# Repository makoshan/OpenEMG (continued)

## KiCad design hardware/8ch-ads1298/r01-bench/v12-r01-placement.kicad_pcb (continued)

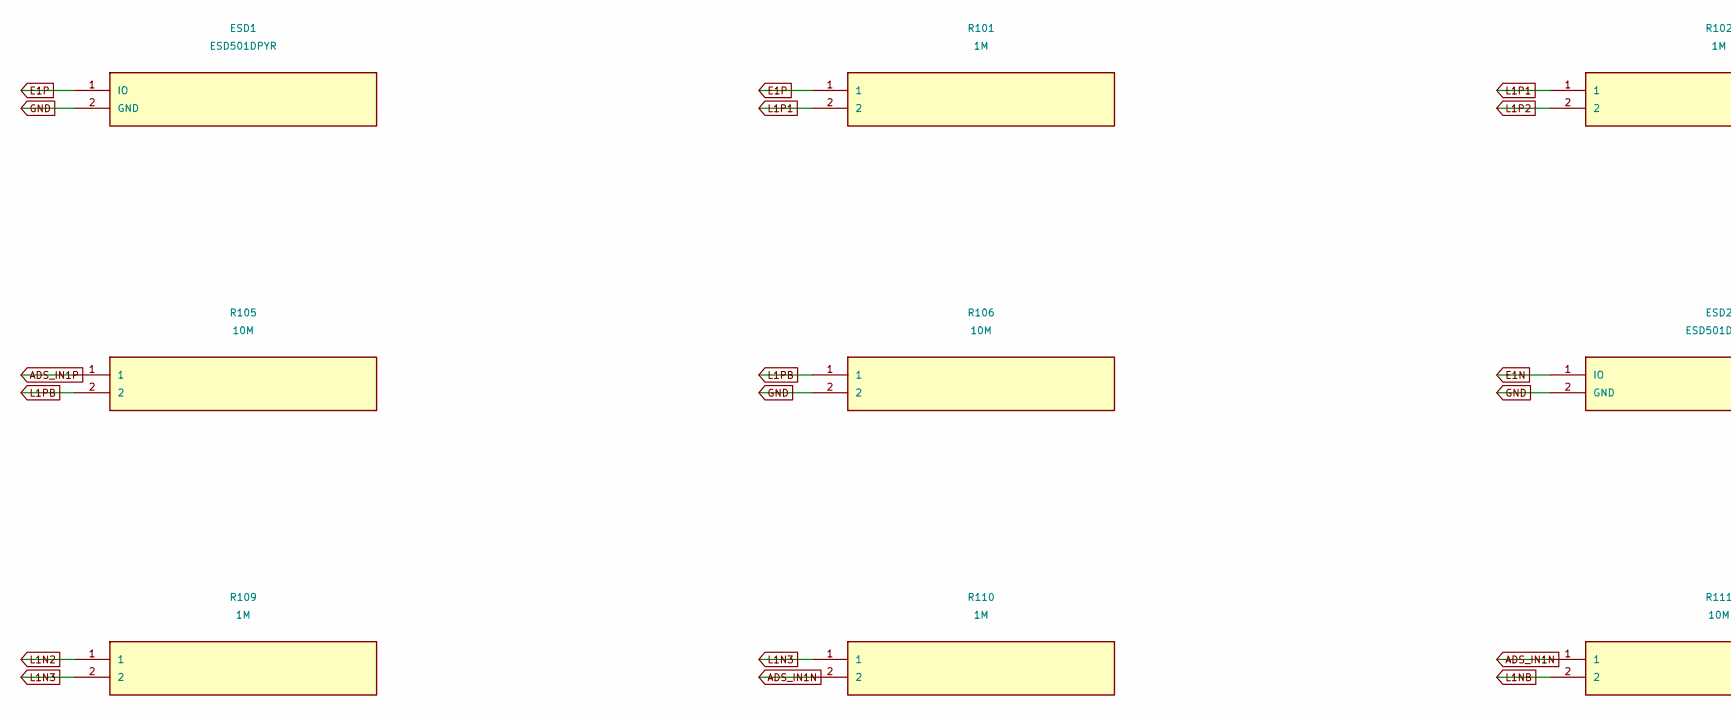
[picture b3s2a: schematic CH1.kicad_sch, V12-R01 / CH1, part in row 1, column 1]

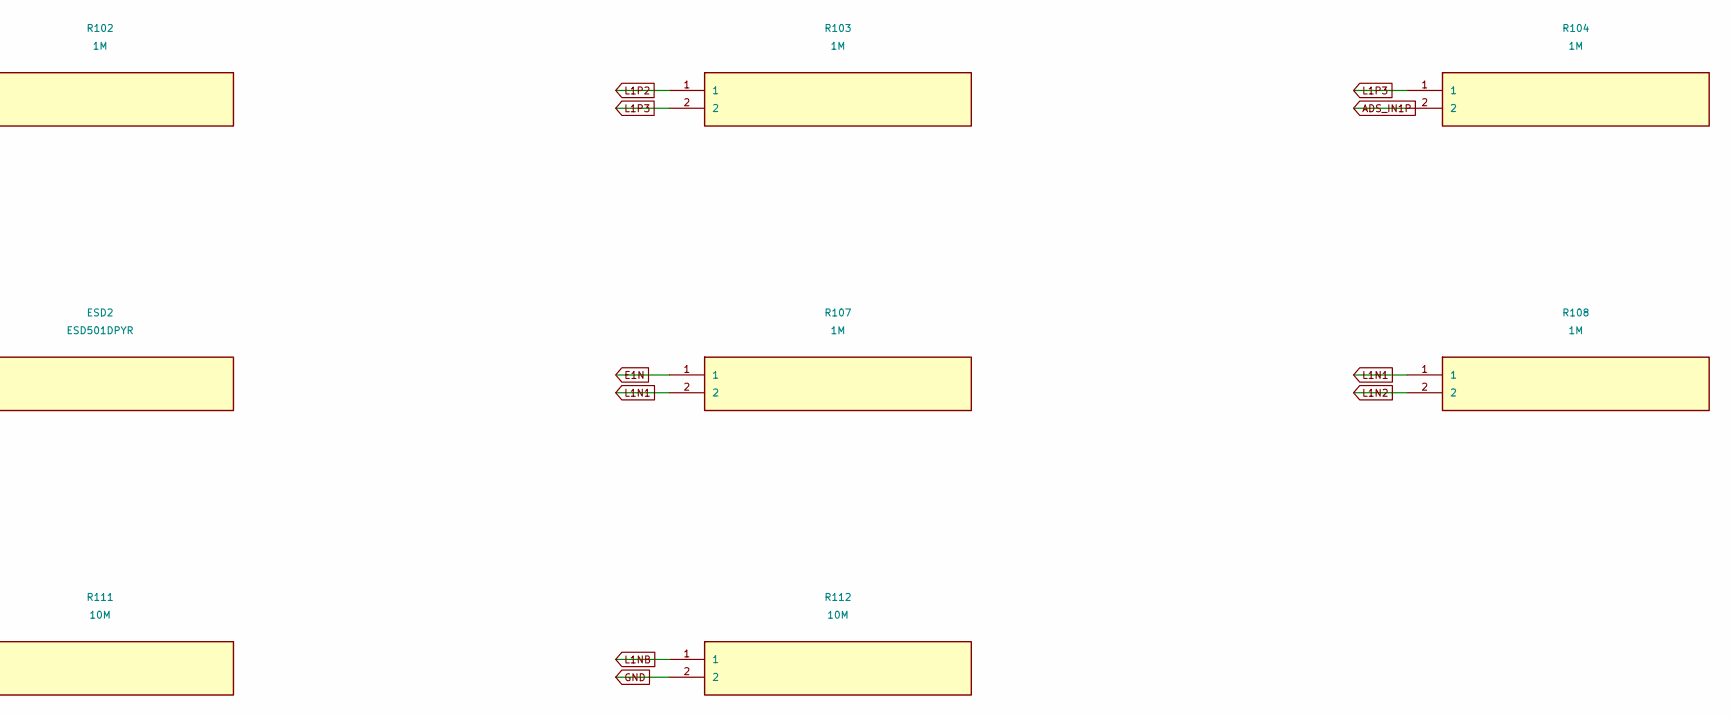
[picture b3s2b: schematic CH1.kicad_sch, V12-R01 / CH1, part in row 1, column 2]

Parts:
ESD1, ESD2: ESD501DPYR; Texas_DPY0002A_0.6x1mm_P0.65mm
R101, R102, R103, R104, R107, R108, R109, R110: 1M; R_0402_1005Metric
R105, R106, R111, R112: 10M; R_0402_1005Metric

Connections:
ADS_IN1N: R110.2, R111.1; also elsewhere on the board
ADS_IN1P: R104.2, R105.1; also elsewhere on the board
E1N: ESD2.1 (IO), R107.1; also elsewhere on the board
E1P: ESD1.1 (IO), R101.1; also elsewhere on the board
GND: ESD1.2 (GND), ESD2.2 (GND), R106.2, R112.2; also elsewhere on the board
L1N1: R107.2, R108.1
L1N2: R108.2, R109.1
L1N3: R109.2, R110.1
L1NB: R111.2, R112.1
L1P1: R101.2, R102.1
L1P2: R102.2, R103.1
L1P3: R103.2, R104.1
L1PB: R105.2, R106.1

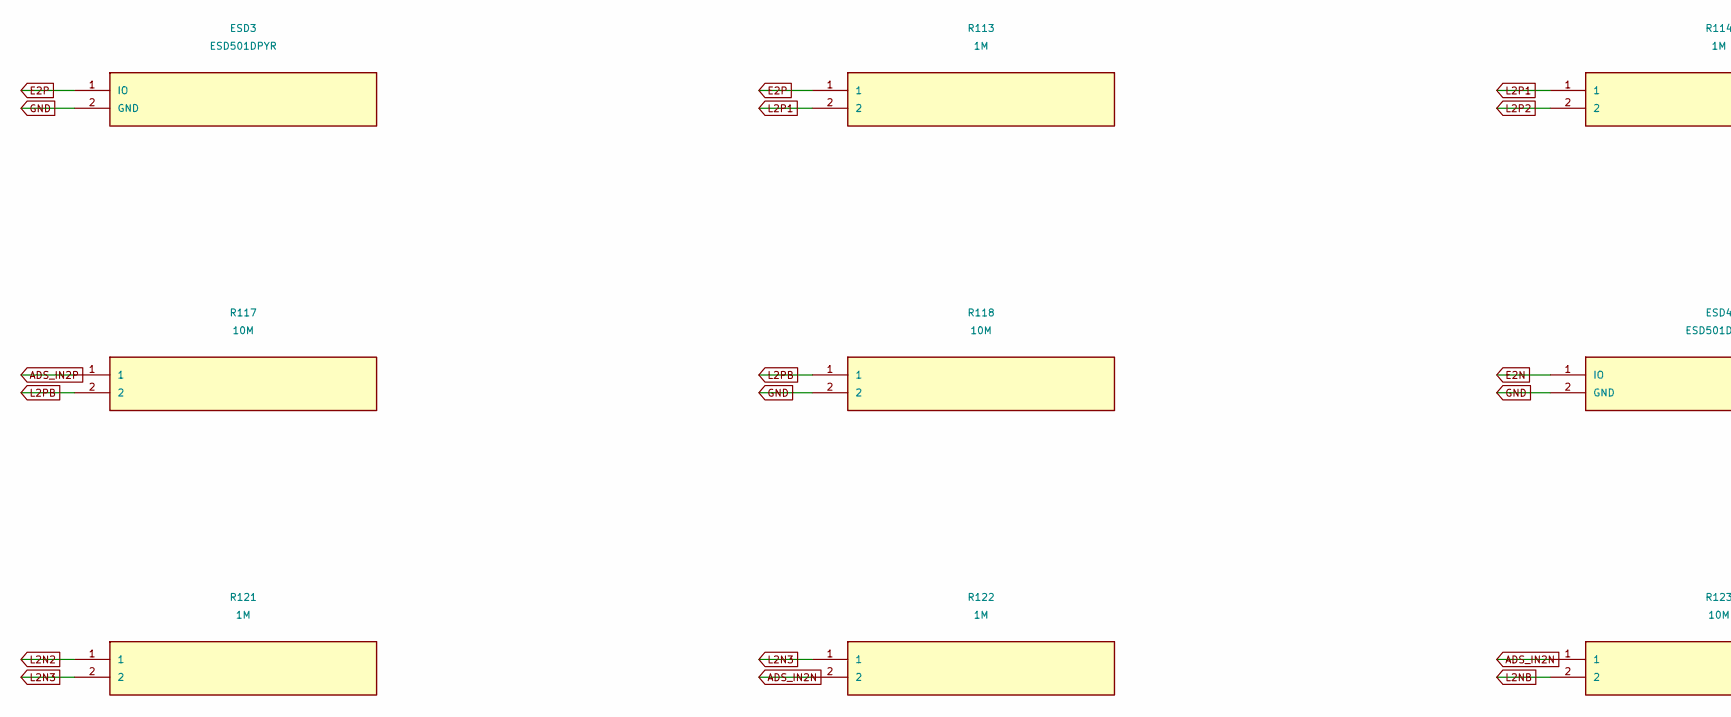
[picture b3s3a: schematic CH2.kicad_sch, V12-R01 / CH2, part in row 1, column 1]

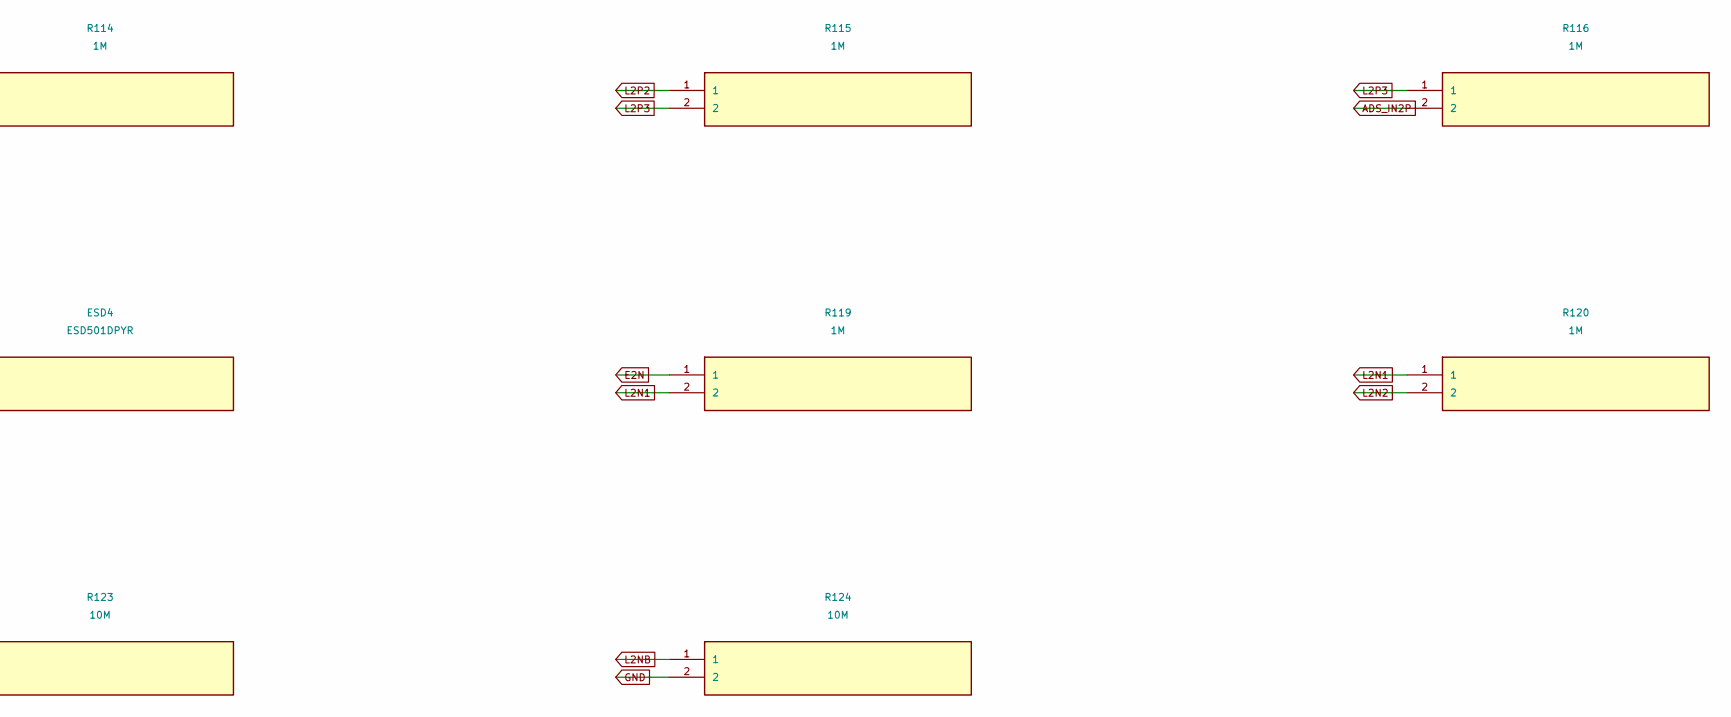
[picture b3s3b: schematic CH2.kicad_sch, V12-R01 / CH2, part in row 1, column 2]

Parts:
ESD3, ESD4: ESD501DPYR; Texas_DPY0002A_0.6x1mm_P0.65mm
R113, R114, R115, R116, R119, R120, R121, R122: 1M; R_0402_1005Metric
R117, R118, R123, R124: 10M; R_0402_1005Metric

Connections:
ADS_IN2N: R122.2, R123.1; also elsewhere on the board
ADS_IN2P: R116.2, R117.1; also elsewhere on the board
E2N: ESD4.1 (IO), R119.1; also elsewhere on the board
E2P: ESD3.1 (IO), R113.1; also elsewhere on the board
GND: ESD3.2 (GND), ESD4.2 (GND), R118.2, R124.2; also elsewhere on the board
L2N1: R119.2, R120.1
L2N2: R120.2, R121.1
L2N3: R121.2, R122.1
L2NB: R123.2, R124.1
L2P1: R113.2, R114.1
L2P2: R114.2, R115.1
L2P3: R115.2, R116.1
L2PB: R117.2, R118.1

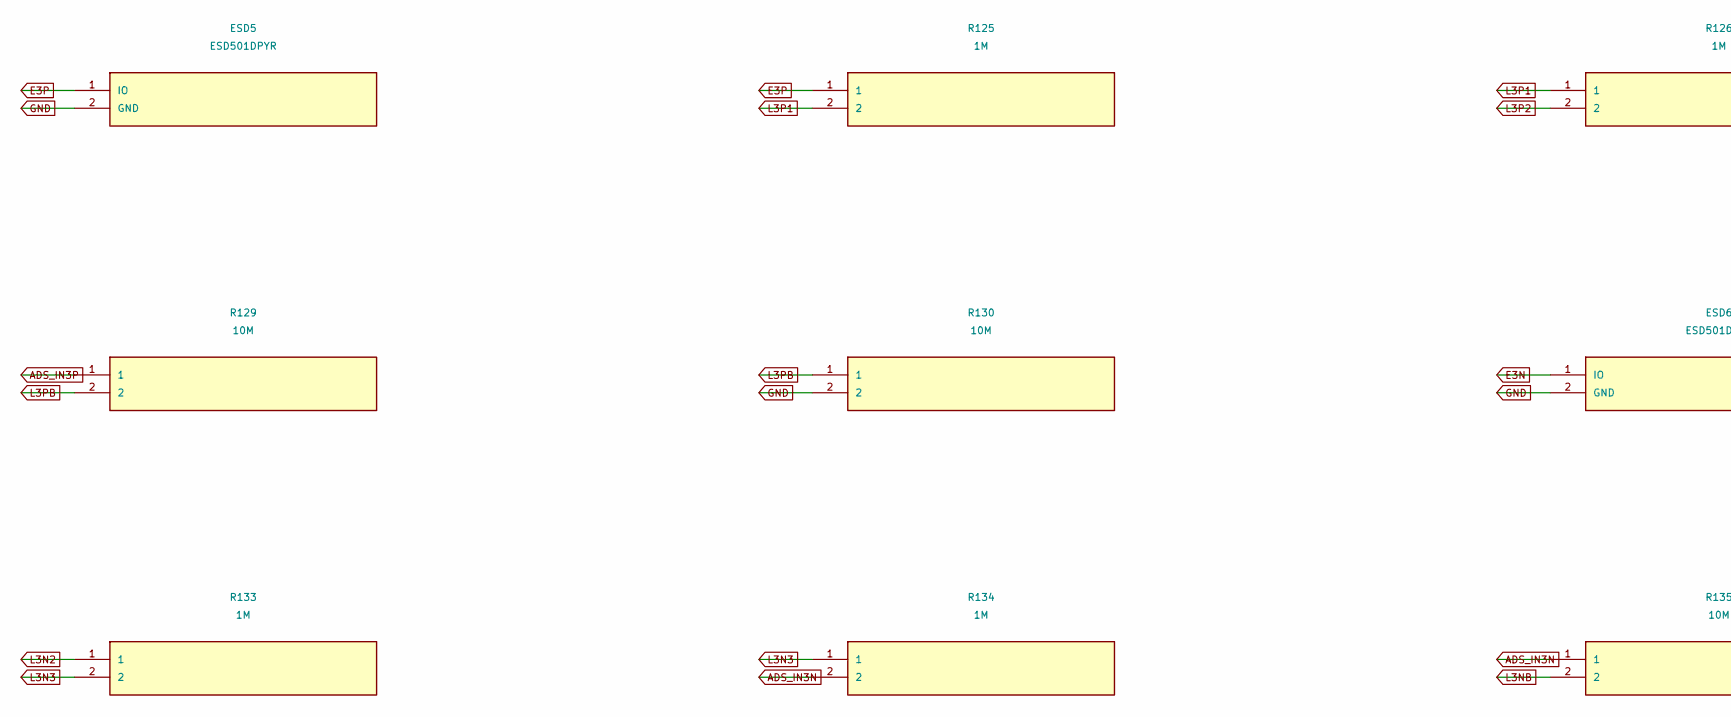
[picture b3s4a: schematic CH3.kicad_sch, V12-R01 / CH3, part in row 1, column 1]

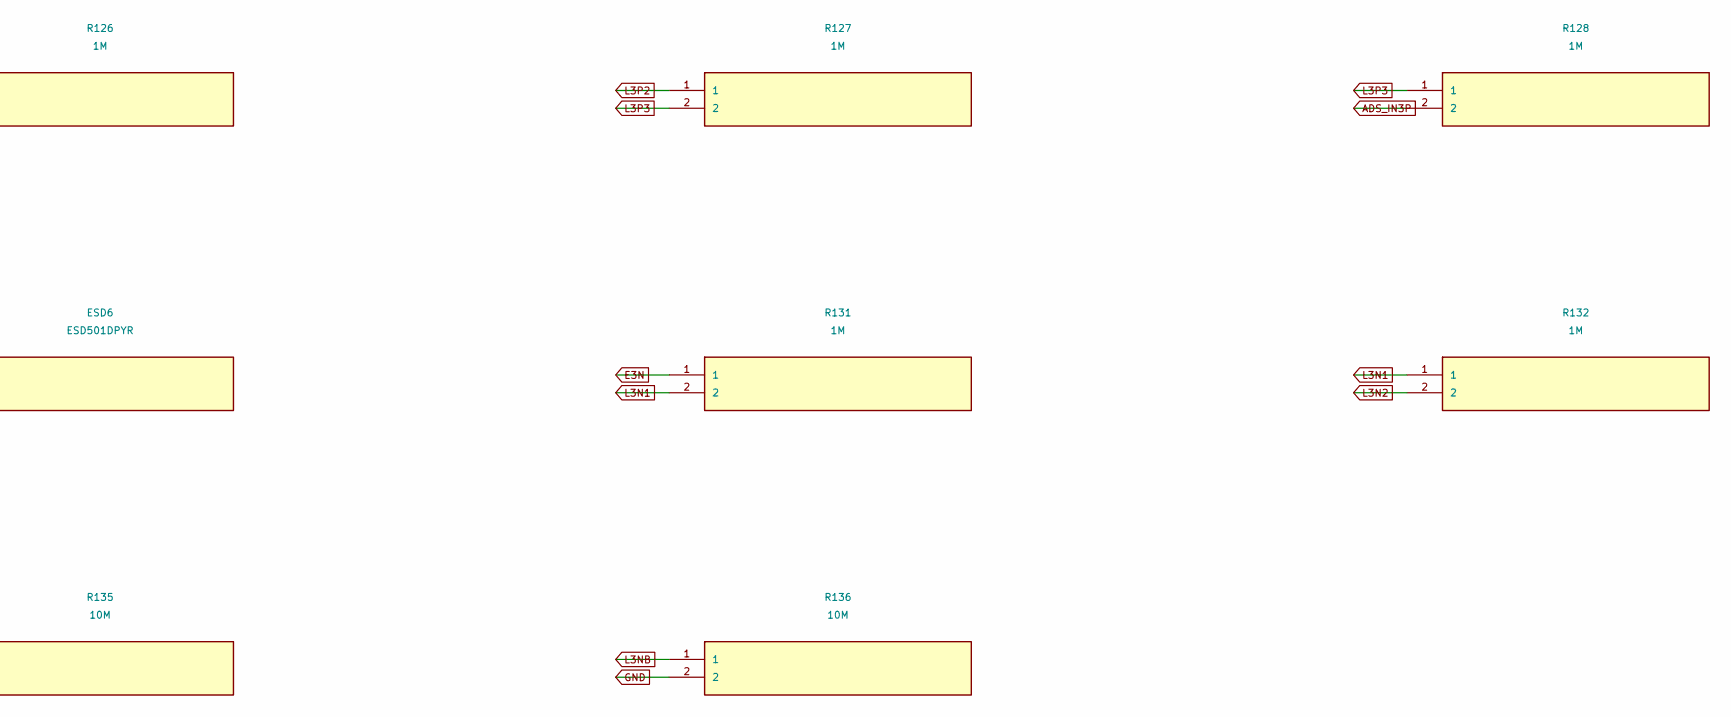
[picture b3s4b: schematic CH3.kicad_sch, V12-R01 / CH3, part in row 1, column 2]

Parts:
ESD5, ESD6: ESD501DPYR; Texas_DPY0002A_0.6x1mm_P0.65mm
R125, R126, R127, R128, R131, R132, R133, R134: 1M; R_0402_1005Metric
R129, R130, R135, R136: 10M; R_0402_1005Metric

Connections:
ADS_IN3N: R134.2, R135.1; also elsewhere on the board
ADS_IN3P: R128.2, R129.1; also elsewhere on the board
E3N: ESD6.1 (IO), R131.1; also elsewhere on the board
E3P: ESD5.1 (IO), R125.1; also elsewhere on the board
GND: ESD5.2 (GND), ESD6.2 (GND), R130.2, R136.2; also elsewhere on the board
L3N1: R131.2, R132.1
L3N2: R132.2, R133.1
L3N3: R133.2, R134.1
L3NB: R135.2, R136.1
L3P1: R125.2, R126.1
L3P2: R126.2, R127.1
L3P3: R127.2, R128.1
L3PB: R129.2, R130.1

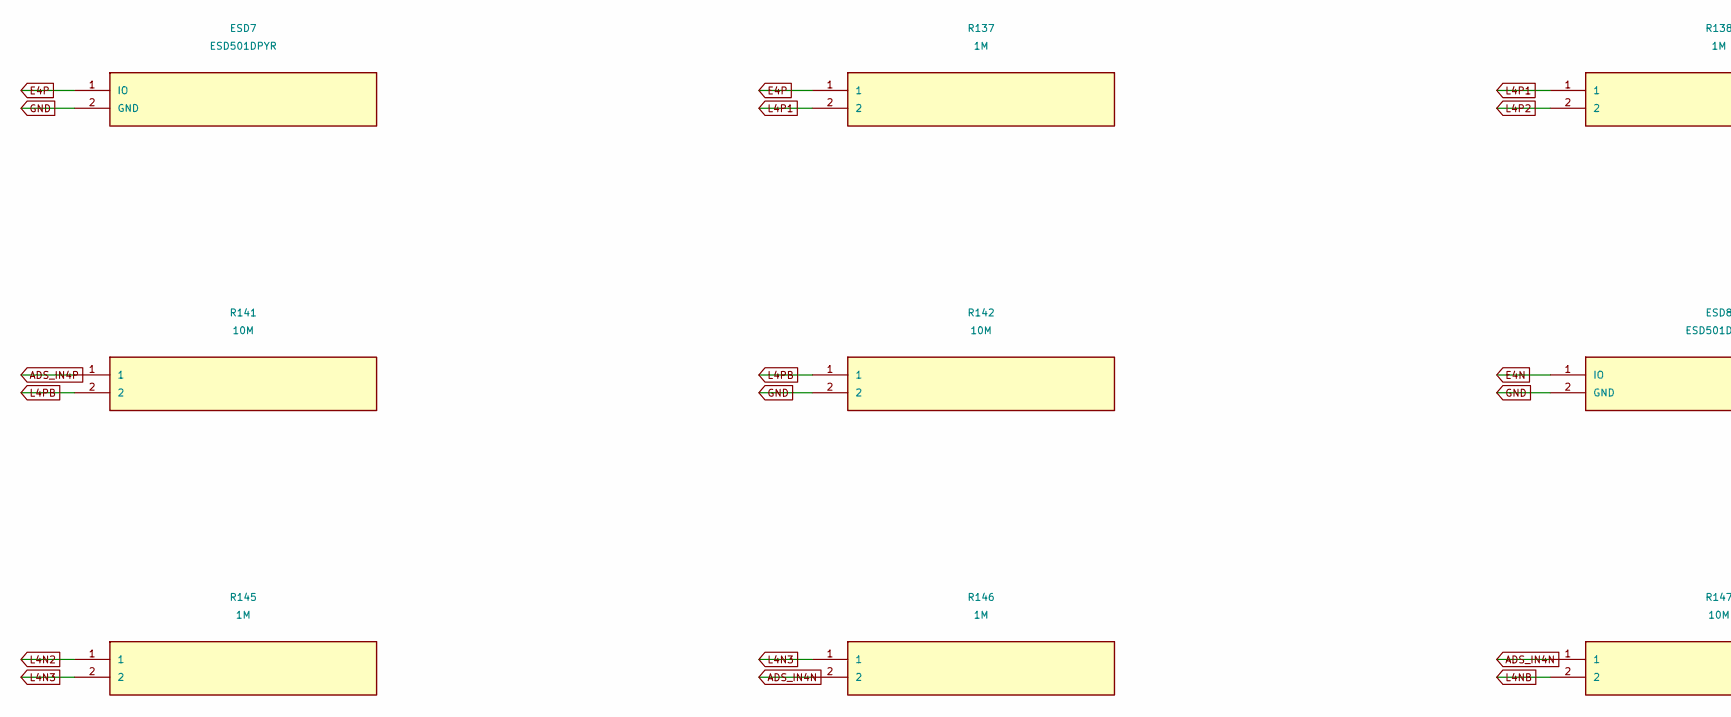
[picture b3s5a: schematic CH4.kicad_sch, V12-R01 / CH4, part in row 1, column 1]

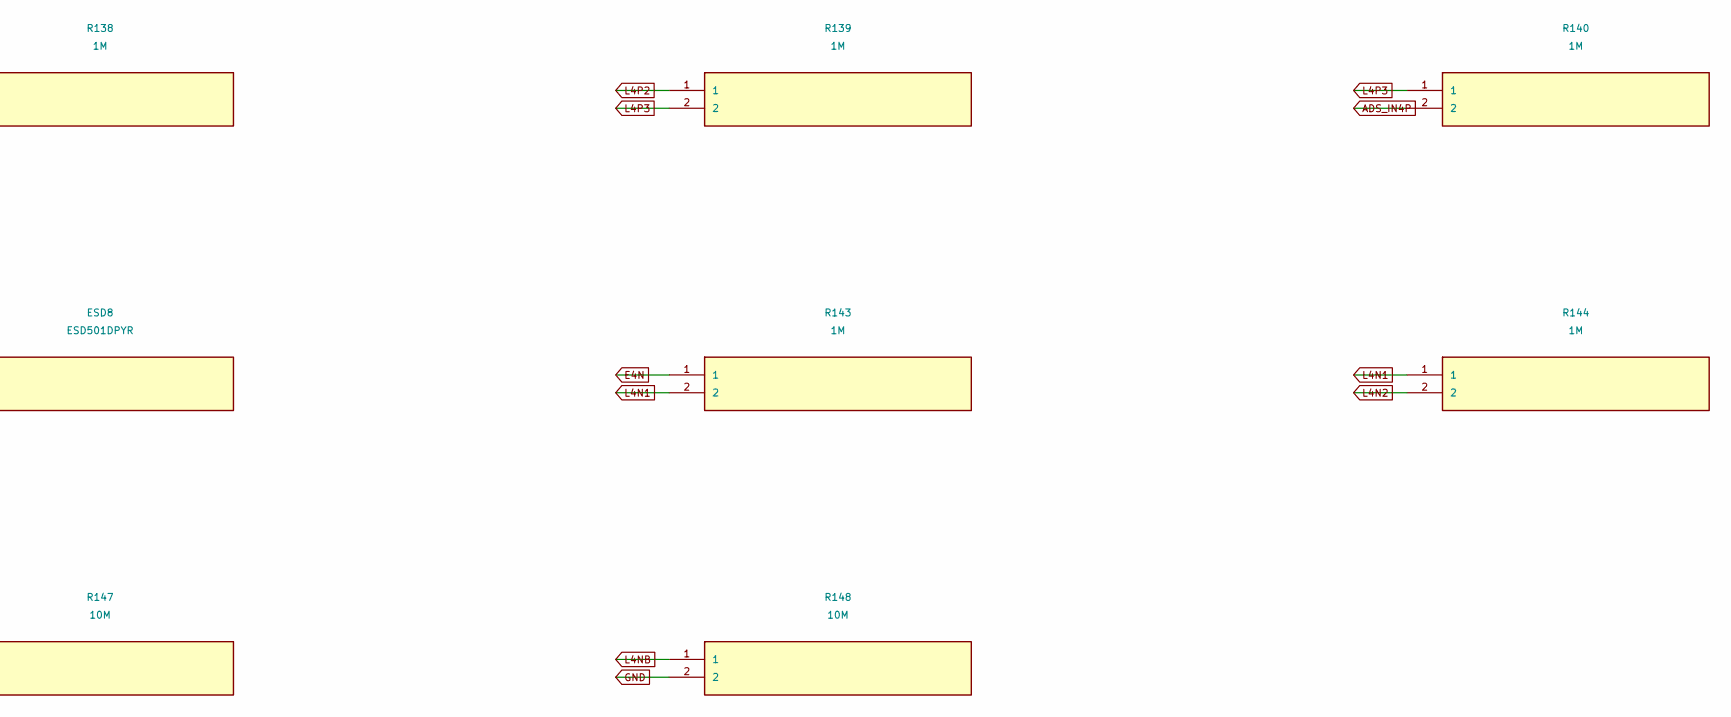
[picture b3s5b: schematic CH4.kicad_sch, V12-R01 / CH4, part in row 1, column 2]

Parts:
ESD7, ESD8: ESD501DPYR; Texas_DPY0002A_0.6x1mm_P0.65mm
R137, R138, R139, R140, R143, R144, R145, R146: 1M; R_0402_1005Metric
R141, R142, R147, R148: 10M; R_0402_1005Metric

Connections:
ADS_IN4N: R146.2, R147.1; also elsewhere on the board
ADS_IN4P: R140.2, R141.1; also elsewhere on the board
E4N: ESD8.1 (IO), R143.1; also elsewhere on the board
E4P: ESD7.1 (IO), R137.1; also elsewhere on the board
GND: ESD7.2 (GND), ESD8.2 (GND), R142.2, R148.2; also elsewhere on the board
L4N1: R143.2, R144.1
L4N2: R144.2, R145.1
L4N3: R145.2, R146.1
L4NB: R147.2, R148.1
L4P1: R137.2, R138.1
L4P2: R138.2, R139.1
L4P3: R139.2, R140.1
L4PB: R141.2, R142.1

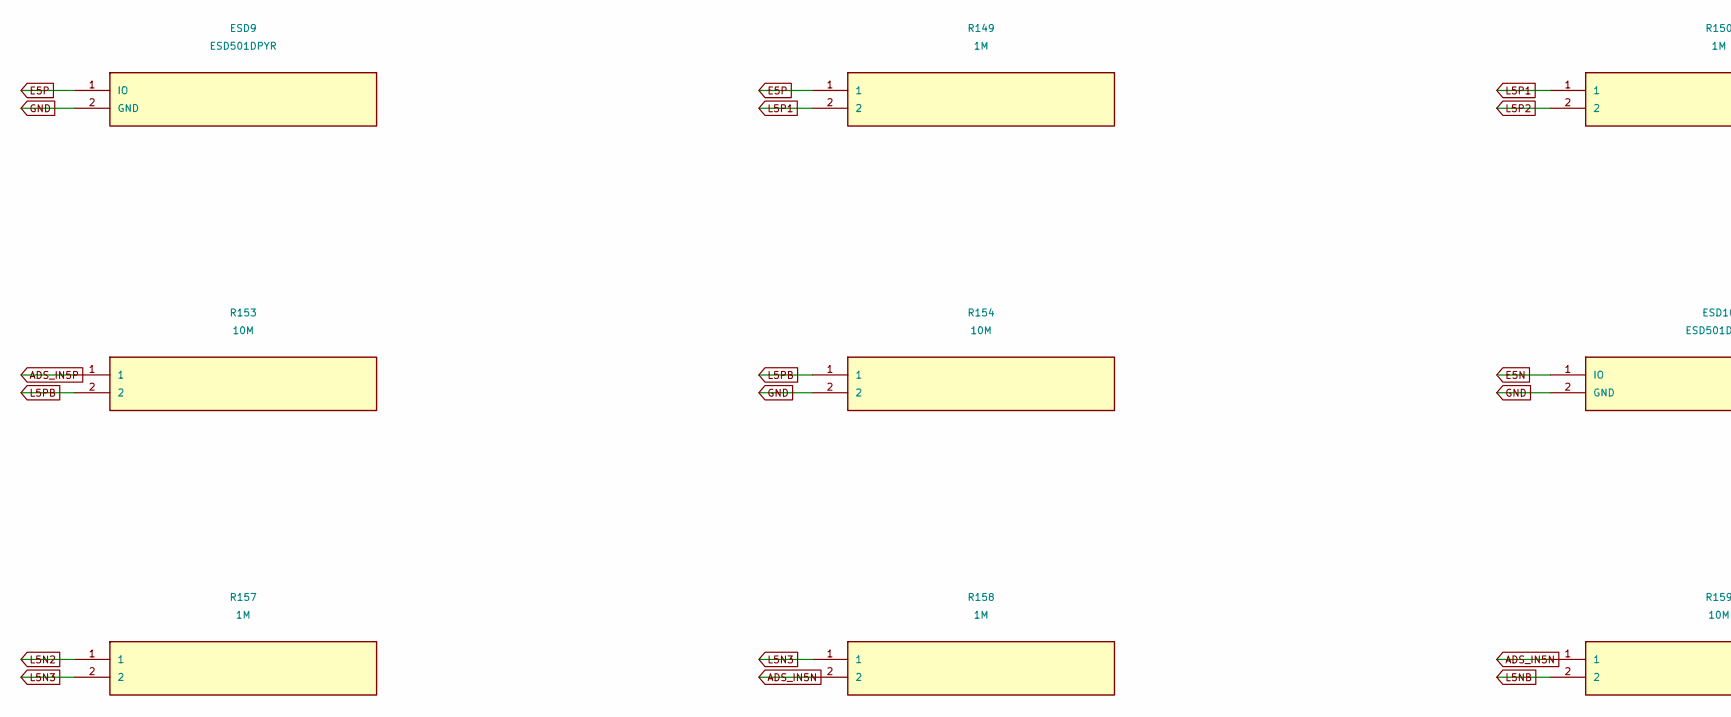
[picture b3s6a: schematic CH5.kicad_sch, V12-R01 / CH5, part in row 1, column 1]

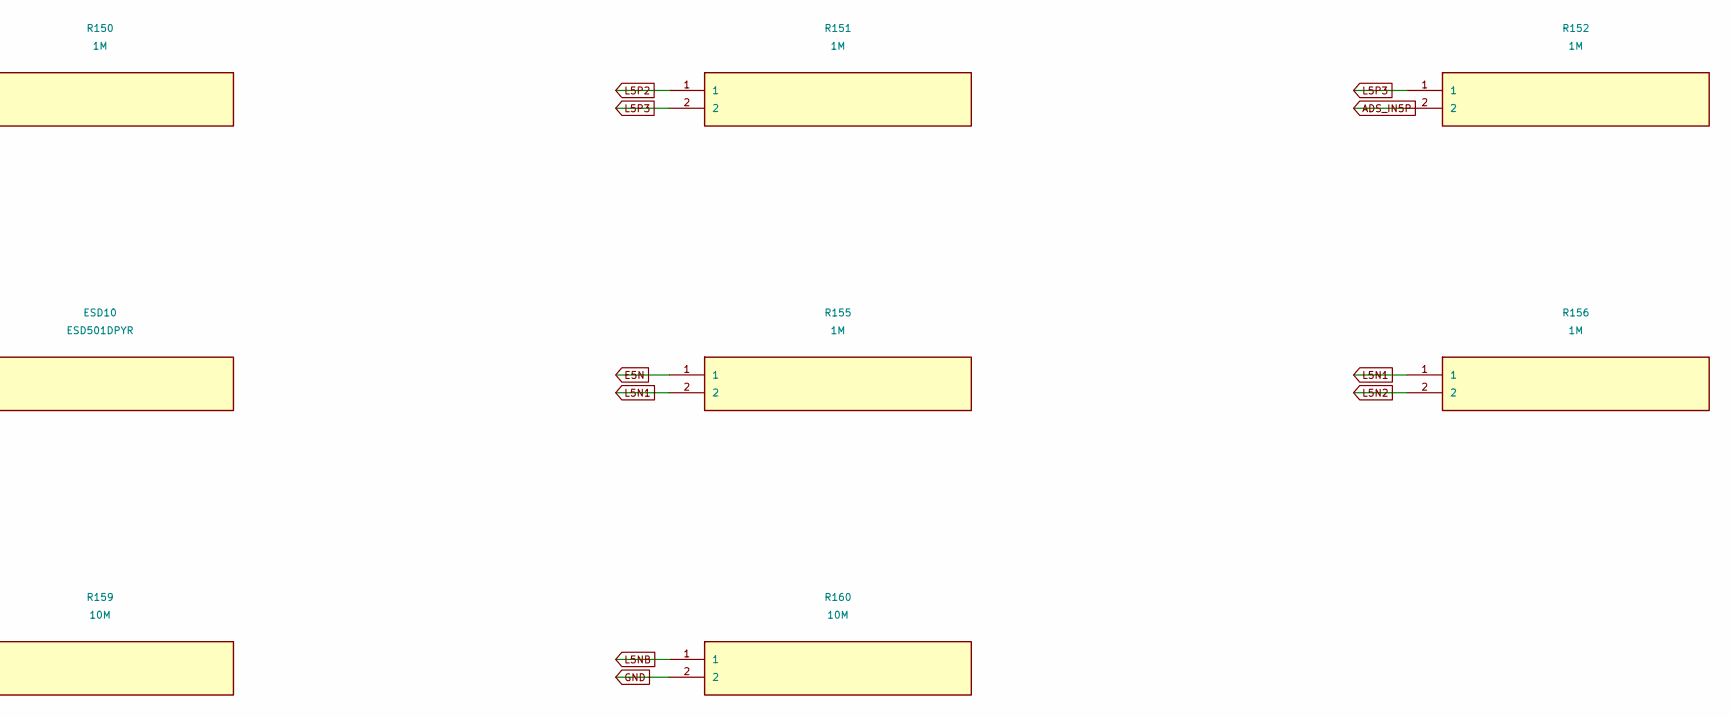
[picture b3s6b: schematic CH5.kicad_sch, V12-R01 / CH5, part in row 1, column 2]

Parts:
ESD9, ESD10: ESD501DPYR; Texas_DPY0002A_0.6x1mm_P0.65mm
R149, R150, R151, R152, R155, R156, R157, R158: 1M; R_0402_1005Metric
R153, R154, R159, R160: 10M; R_0402_1005Metric

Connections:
ADS_IN5N: R158.2, R159.1; also elsewhere on the board
ADS_IN5P: R152.2, R153.1; also elsewhere on the board
E5N: ESD10.1 (IO), R155.1; also elsewhere on the board
E5P: ESD9.1 (IO), R149.1; also elsewhere on the board
GND: ESD9.2 (GND), ESD10.2 (GND), R154.2, R160.2; also elsewhere on the board
L5N1: R155.2, R156.1
L5N2: R156.2, R157.1
L5N3: R157.2, R158.1
L5NB: R159.2, R160.1
L5P1: R149.2, R150.1
L5P2: R150.2, R151.1
L5P3: R151.2, R152.1
L5PB: R153.2, R154.1

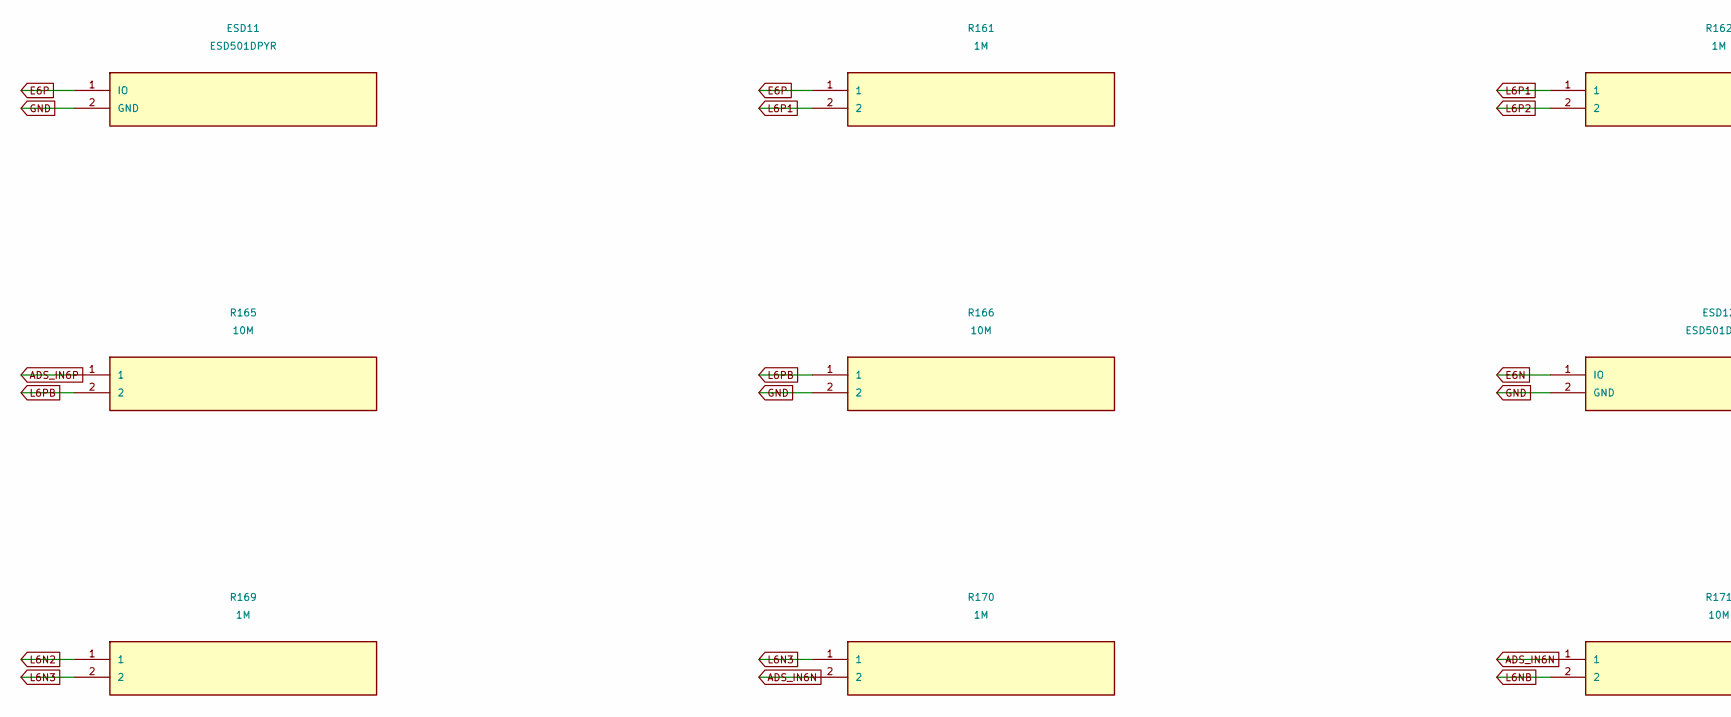
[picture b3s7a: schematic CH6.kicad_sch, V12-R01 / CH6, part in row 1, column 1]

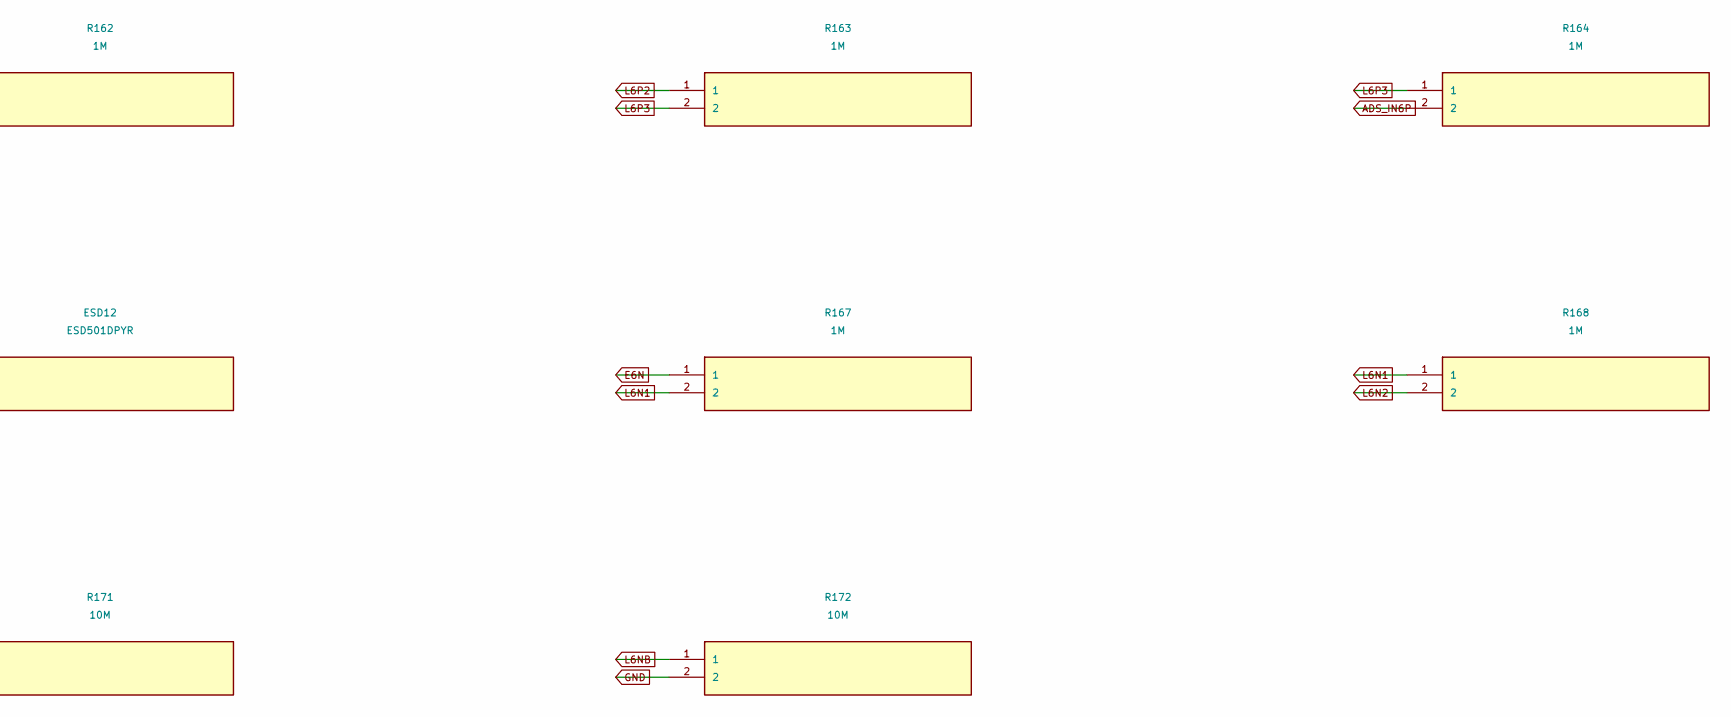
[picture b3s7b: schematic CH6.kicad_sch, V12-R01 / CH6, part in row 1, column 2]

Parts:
ESD11, ESD12: ESD501DPYR; Texas_DPY0002A_0.6x1mm_P0.65mm
R161, R162, R163, R164, R167, R168, R169, R170: 1M; R_0402_1005Metric
R165, R166, R171, R172: 10M; R_0402_1005Metric

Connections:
ADS_IN6N: R170.2, R171.1; also elsewhere on the board
ADS_IN6P: R164.2, R165.1; also elsewhere on the board
E6N: ESD12.1 (IO), R167.1; also elsewhere on the board
E6P: ESD11.1 (IO), R161.1; also elsewhere on the board
GND: ESD11.2 (GND), ESD12.2 (GND), R166.2, R172.2; also elsewhere on the board
L6N1: R167.2, R168.1
L6N2: R168.2, R169.1
L6N3: R169.2, R170.1
L6NB: R171.2, R172.1
L6P1: R161.2, R162.1
L6P2: R162.2, R163.1
L6P3: R163.2, R164.1
L6PB: R165.2, R166.1

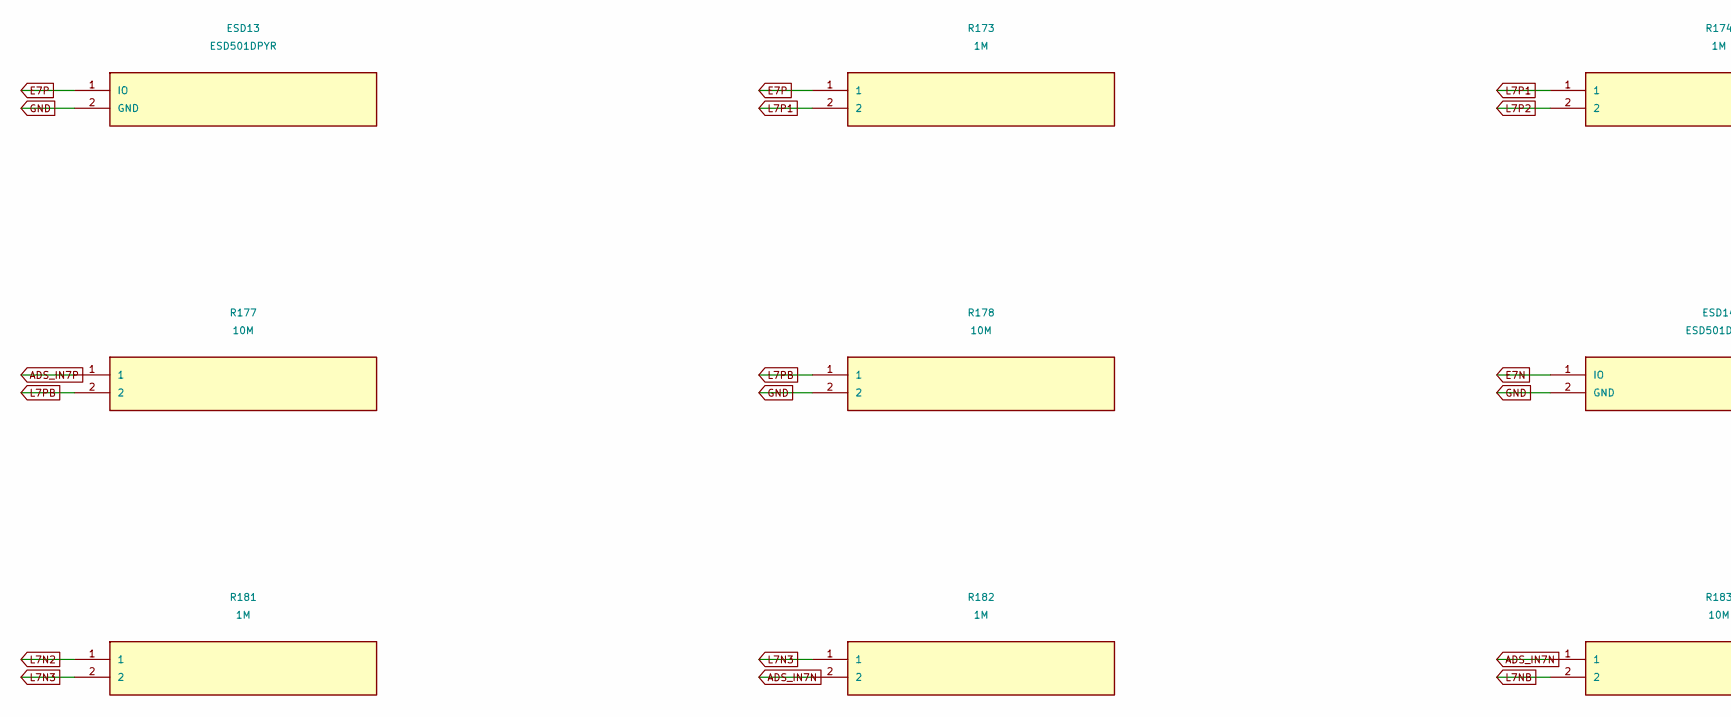
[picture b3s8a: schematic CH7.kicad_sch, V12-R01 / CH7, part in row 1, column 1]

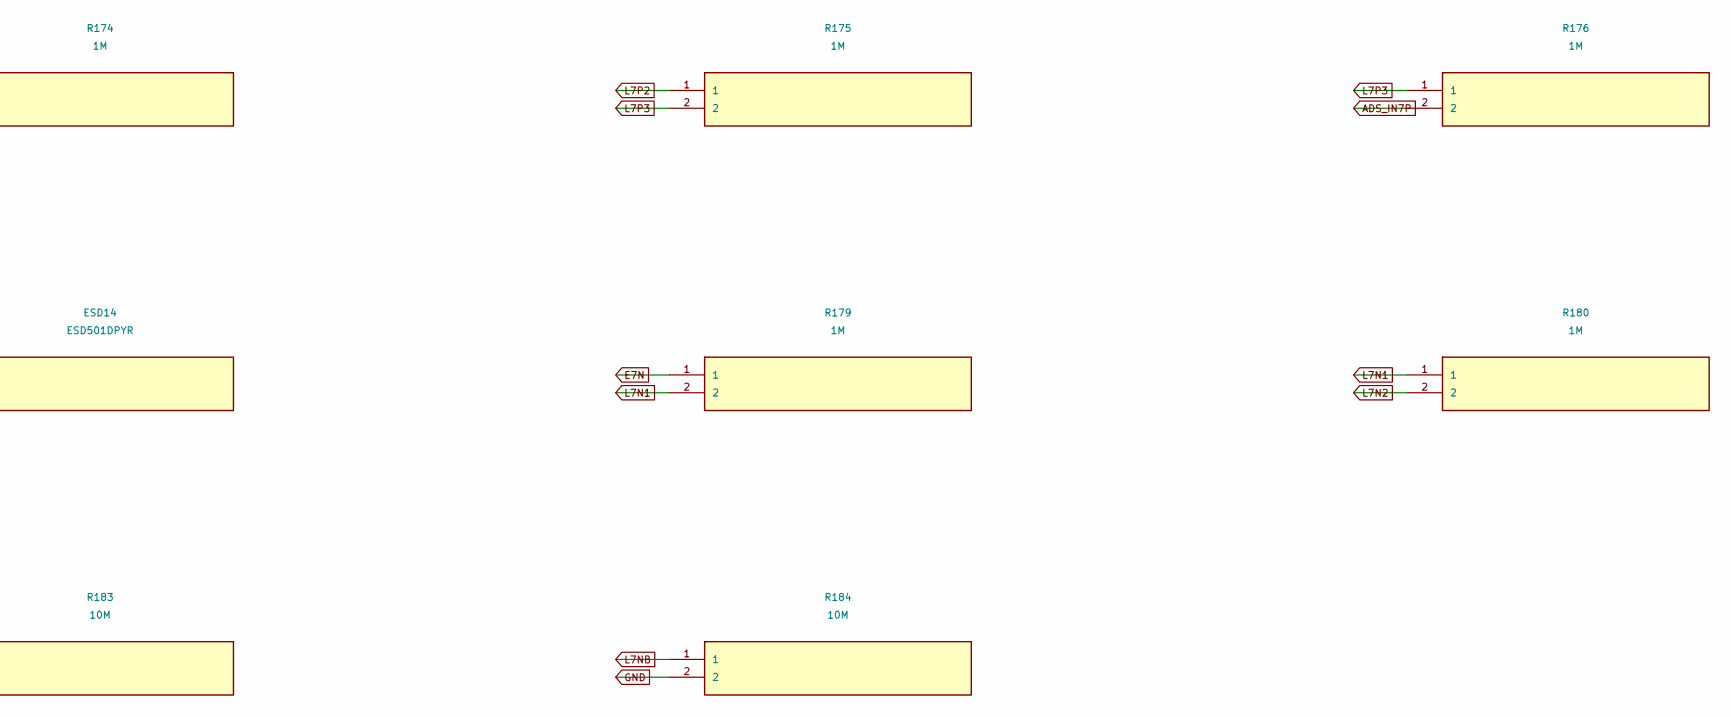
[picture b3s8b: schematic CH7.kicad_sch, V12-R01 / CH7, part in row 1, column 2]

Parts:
ESD13, ESD14: ESD501DPYR; Texas_DPY0002A_0.6x1mm_P0.65mm
R173, R174, R175, R176, R179, R180, R181, R182: 1M; R_0402_1005Metric
R177, R178, R183, R184: 10M; R_0402_1005Metric

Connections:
ADS_IN7N: R182.2, R183.1; also elsewhere on the board
ADS_IN7P: R176.2, R177.1; also elsewhere on the board
E7N: ESD14.1 (IO), R179.1; also elsewhere on the board
E7P: ESD13.1 (IO), R173.1; also elsewhere on the board
GND: ESD13.2 (GND), ESD14.2 (GND), R178.2, R184.2; also elsewhere on the board
L7N1: R179.2, R180.1
L7N2: R180.2, R181.1
L7N3: R181.2, R182.1
L7NB: R183.2, R184.1
L7P1: R173.2, R174.1
L7P2: R174.2, R175.1
L7P3: R175.2, R176.1
L7PB: R177.2, R178.1

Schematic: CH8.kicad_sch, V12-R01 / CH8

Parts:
ESD15, ESD16: ESD501DPYR; Texas_DPY0002A_0.6x1mm_P0.65mm
R185, R186, R187, R188, R191, R192, R193, R194: 1M; R_0402_1005Metric
R189, R190, R195, R196: 10M; R_0402_1005Metric

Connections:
ADS_IN8N: R194.2, R195.1; also elsewhere on the board
ADS_IN8P: R188.2, R189.1; also elsewhere on the board
E8N: ESD16.1 (IO), R191.1; also elsewhere on the board
E8P: ESD15.1 (IO), R185.1; also elsewhere on the board
GND: ESD15.2 (GND), ESD16.2 (GND), R190.2, R196.2; also elsewhere on the board
L8N1: R191.2, R192.1
L8N2: R192.2, R193.1
L8N3: R193.2, R194.1
L8NB: R195.2, R196.1
L8P1: R185.2, R186.1
L8P2: R186.2, R187.1
L8P3: R187.2, R188.1
L8PB: R189.2, R190.1

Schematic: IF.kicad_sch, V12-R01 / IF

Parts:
C26, C27, C28, C29, C30: 100nF; C_0402_1005Metric
J1: XIAO_16P; Samtec_TST-108-01-L-D
J2: BAT_2P; JST_PH_B2B-PH-K_1x02_P2.00mm_Vertical
J3: ELECTRODE_17P; Molex_Micro-Fit_3.0_43045-2012_2x10_P3.00mm_Vertical
R33, R34, R35, R36, R37, R38, R39: 10k; R_0402_1005Metric
U2, U3: SN74AXC8T245RHLR; TI_RHL0024A
U10: SN74AUP1T14DCKR; SOT-353_SC-70-5

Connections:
3V3: C26.1, C28.1, C30.1, J1.1 (3V3), R33.2, U2.1 (VCCA), U2.2 (DIR1), U3.1 (VCCA), U10.5 (VCC); also elsewhere on the board
ADS_CLKSEL: U2.17 (B5); also elsewhere on the board
ADS_CS: U2.21 (B1); also elsewhere on the board
ADS_DRDY: U3.20 (B2); also elsewhere on the board
ADS_PWDN: U2.16 (B6); also elsewhere on the board
ADS_RESET: U2.18 (B4); also elsewhere on the board
ANA_EN: J1.10 (D0_ANA_EN); also elsewhere on the board
AVDD_SENSE: J1.11 (D3_AVDD_SENSE); also elsewhere on the board
DIN_B: U2.19 (B3); also elsewhere on the board
DOUT_B: U3.21 (B1); also elsewhere on the board
DVDD: C27.1, C29.1, U2.23 (VCCB), U2.24 (VCCB), U3.23 (VCCB), U3.24 (VCCB); also elsewhere on the board
E1N: J3.2 (E1N); also elsewhere on the board
E1P: J3.1 (E1P); also elsewhere on the board
E2N: J3.4 (E2N); also elsewhere on the board
E2P: J3.3 (E2P); also elsewhere on the board
E3N: J3.6 (E3N); also elsewhere on the board
E3P: J3.5 (E3P); also elsewhere on the board
E4N: J3.8 (E4N); also elsewhere on the board
E4P: J3.7 (E4P); also elsewhere on the board
E5N: J3.10 (E5N); also elsewhere on the board
E5P: J3.9 (E5P); also elsewhere on the board
E6N: J3.12 (E6N); also elsewhere on the board
E6P: J3.11 (E6P); also elsewhere on the board
E7N: J3.14 (E7N); also elsewhere on the board
E7P: J3.13 (E7P); also elsewhere on the board
E8N: J3.16 (E8N); also elsewhere on the board
E8P: J3.15 (E8P); also elsewhere on the board
E_RLD: J3.17 (E_RLD); also elsewhere on the board
GND: C26.2, C27.2, C28.2, C29.2, C30.2, J1.2 (GND), J1.14 (GND), J2.2 (BAT-), R34.2, R35.2, R36.2, R37.2, R38.2, R39.2, U2.9 (A7), U2.10 (A8), U2.11 (DIR2), U2.12 (GND), U2.13 (GND), U2.25 (EP), U3.2 (DIR1), U3.11 (DIR2), U3.12 (GND), U3.13 (GND), U3.14 (B8), U3.15 (B7), U3.16 (B6), U3.17 (B5), U3.18 (B4), U3.19 (B3), U3.25 (EP), U10.3 (GND); also elsewhere on the board
OE_N: J1.16 (D5_NOT_READY), R33.1, U2.22 (OE#), U3.22 (OE#), U10.4 (Y); also elsewhere on the board
PG: U10.2 (A); also elsewhere on the board
SCLK_B: U2.20 (B2); also elsewhere on the board
VBAT: J1.13 (BAT+), J2.1 (BAT+); also elsewhere on the board
VBUS: J1.12 (VBUS_SENSE); also elsewhere on the board
XIAO_CLKSEL: J1.9 (D1_CLKSEL), R38.1, U2.7 (A5)
XIAO_CS: J1.6 (D7_CS), R34.1, U2.3 (A1)
XIAO_DRDY: J1.7 (D6_DRDY), U3.4 (A2)
XIAO_MISO: J1.4 (D9_MISO), U3.3 (A1)
XIAO_MOSI: J1.5 (D10_MOSI), R36.1, U2.5 (A3)
XIAO_PWDN: J1.15 (D4_PWDN), R39.1, U2.8 (A6)
XIAO_RESET: J1.8 (D2_RESET), R37.1, U2.6 (A4)
XIAO_SCLK: J1.3 (D8_SCK), R35.1, U2.4 (A2)
